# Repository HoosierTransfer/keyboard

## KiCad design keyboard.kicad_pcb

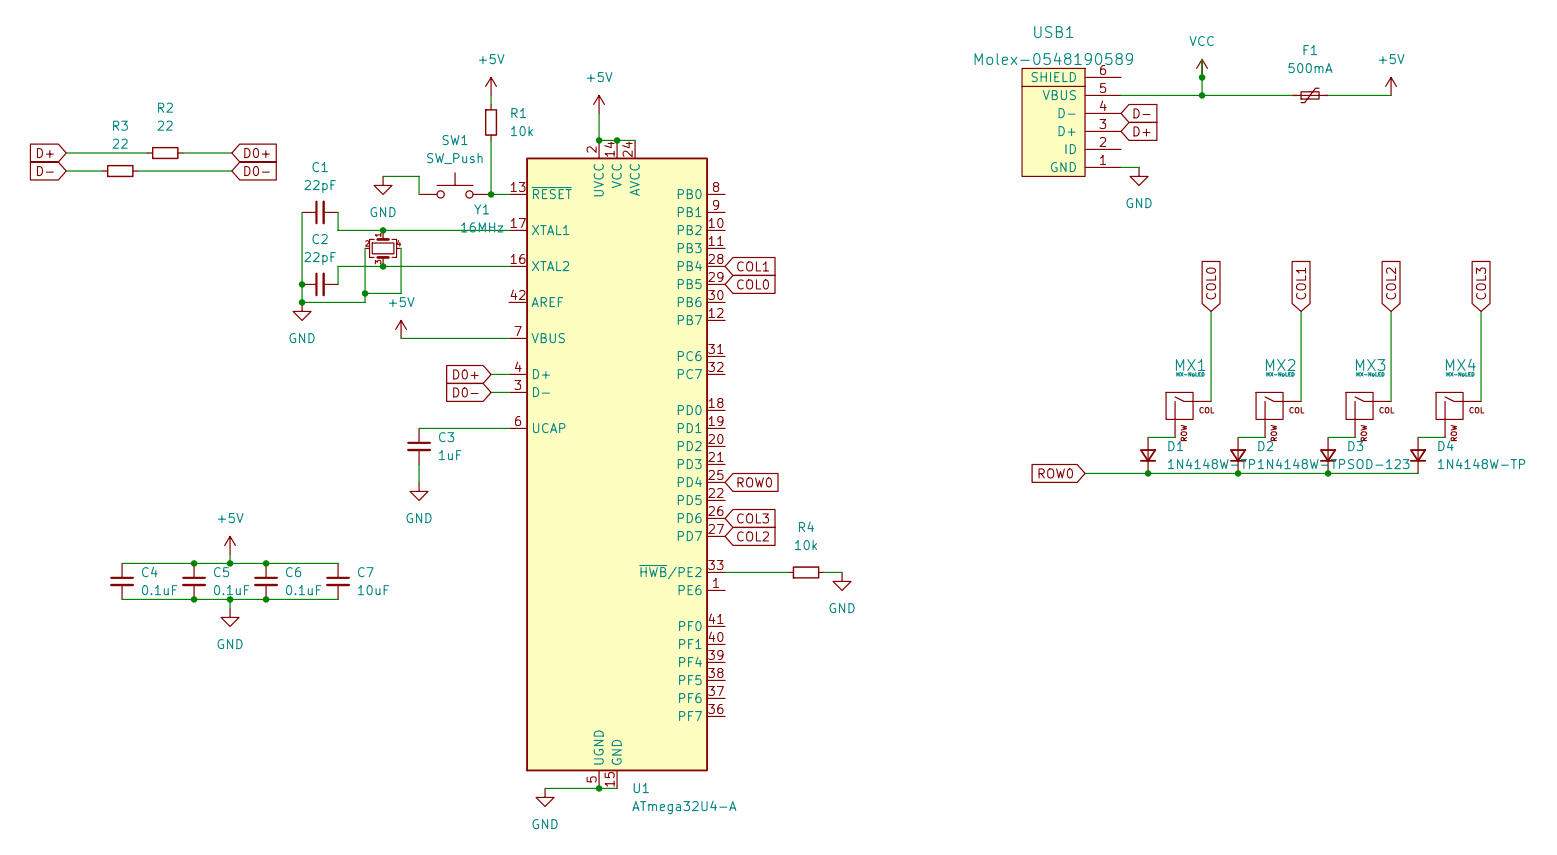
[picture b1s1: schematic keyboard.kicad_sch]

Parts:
C1, C2: 22pF; C_0805_2012Metric; LCSC C1804
C3: 1uF; C_0805_2012Metric; LCSC C116352
C4, C5, C6: 0.1uF; C_0805_2012Metric; LCSC C730459
C7: 10uF; C_0805_2012Metric; LCSC C307520
D1, D2, D4: 1N4148W-TP; D_SOD-123; LCSC C77978
D3: SOD-123; D_SOD-123
F1: 500mA; Fuse_1206_3216Metric; LCSC C170165
MX1, MX2, MX3, MX4: MX-NoLED; MXOnly-1U-NoLED
R1, R4: 10k; R_0805_2012Metric; LCSC C84376
R2, R3: 22; R_0805_2012Metric; LCSC C17561
SW1: SW_Push; SKQG-1155865; LCSC C221929
U1: ATmega32U4-A; TQFP-44_10x10mm_P0.8mm
USB1: Molex-0548190589; LCSC C145778
Y1: 16MHz; Crystal_SMD_3225-4Pin_3.2x2.5mm

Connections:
+5V: C4.1, C5.1, C6.1, C7.1, F1.2, R1.1, U1.2 (UVCC), U1.7 (VBUS), U1.14 (VCC), U1.24 (AVCC), U1.34 (VCC), U1.44 (AVCC)
COL0: MX1.1 (COL), U1.29 (PB5)
COL1: MX2.1 (COL), U1.28 (PB4)
COL2: MX3.1 (COL), U1.27 (PD7)
COL3: MX4.1 (COL), U1.26 (PD6)
D0+: R2.2, U1.4 (D+)
D0-: R3.2, U1.3 (D-)
D+: R2.1, USB1.3 (D+)
D-: R3.1, USB1.4 (D-)
GND: C1.1, C2.1, C3.2, C4.2, C5.2, C6.2, C7.2, R4.2, SW1.1, U1.5 (UGND), U1.15 (GND), U1.23 (GND), U1.35 (GND), U1.43 (GND), USB1.1 (GND), Y1.2, Y1.4
unnamed: C1.2, U1.17 (XTAL1), Y1.1
unnamed: C2.2, U1.16 (XTAL2), Y1.3
unnamed: C3.1, U1.6 (UCAP)
unnamed: D1.2 (A), MX1.2 (ROW)
unnamed: D2.2 (A), MX2.2 (ROW)
unnamed: D3.2 (A), MX3.2 (ROW)
unnamed: D4.2 (A), MX4.2 (ROW)
unnamed: R1.2, SW1.2, U1.13 (~RESET)
unnamed: R4.1, U1.33 (~HWB/PE2)
ROW0: D1.1 (K), D2.1 (K), D3.1 (K), D4.1 (K), U1.25 (PD4)
VCC: F1.1, USB1.5 (VBUS)

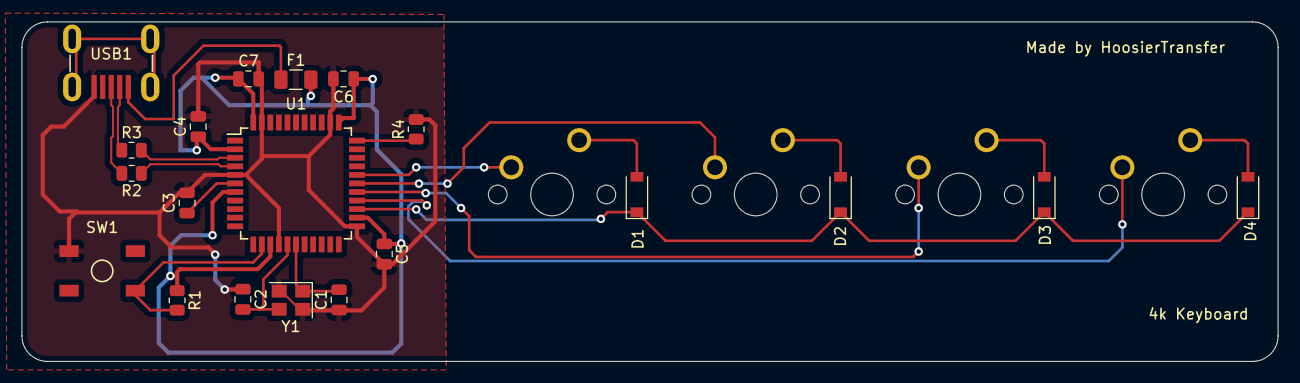
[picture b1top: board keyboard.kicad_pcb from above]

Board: 2 copper layers, 117.5 x 31.8 mm, 24 parts (0 on the bottom side), 21 nets.

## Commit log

2022-06-26 Add submodules
